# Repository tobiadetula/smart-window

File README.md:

# smart-window
detailing my final year project

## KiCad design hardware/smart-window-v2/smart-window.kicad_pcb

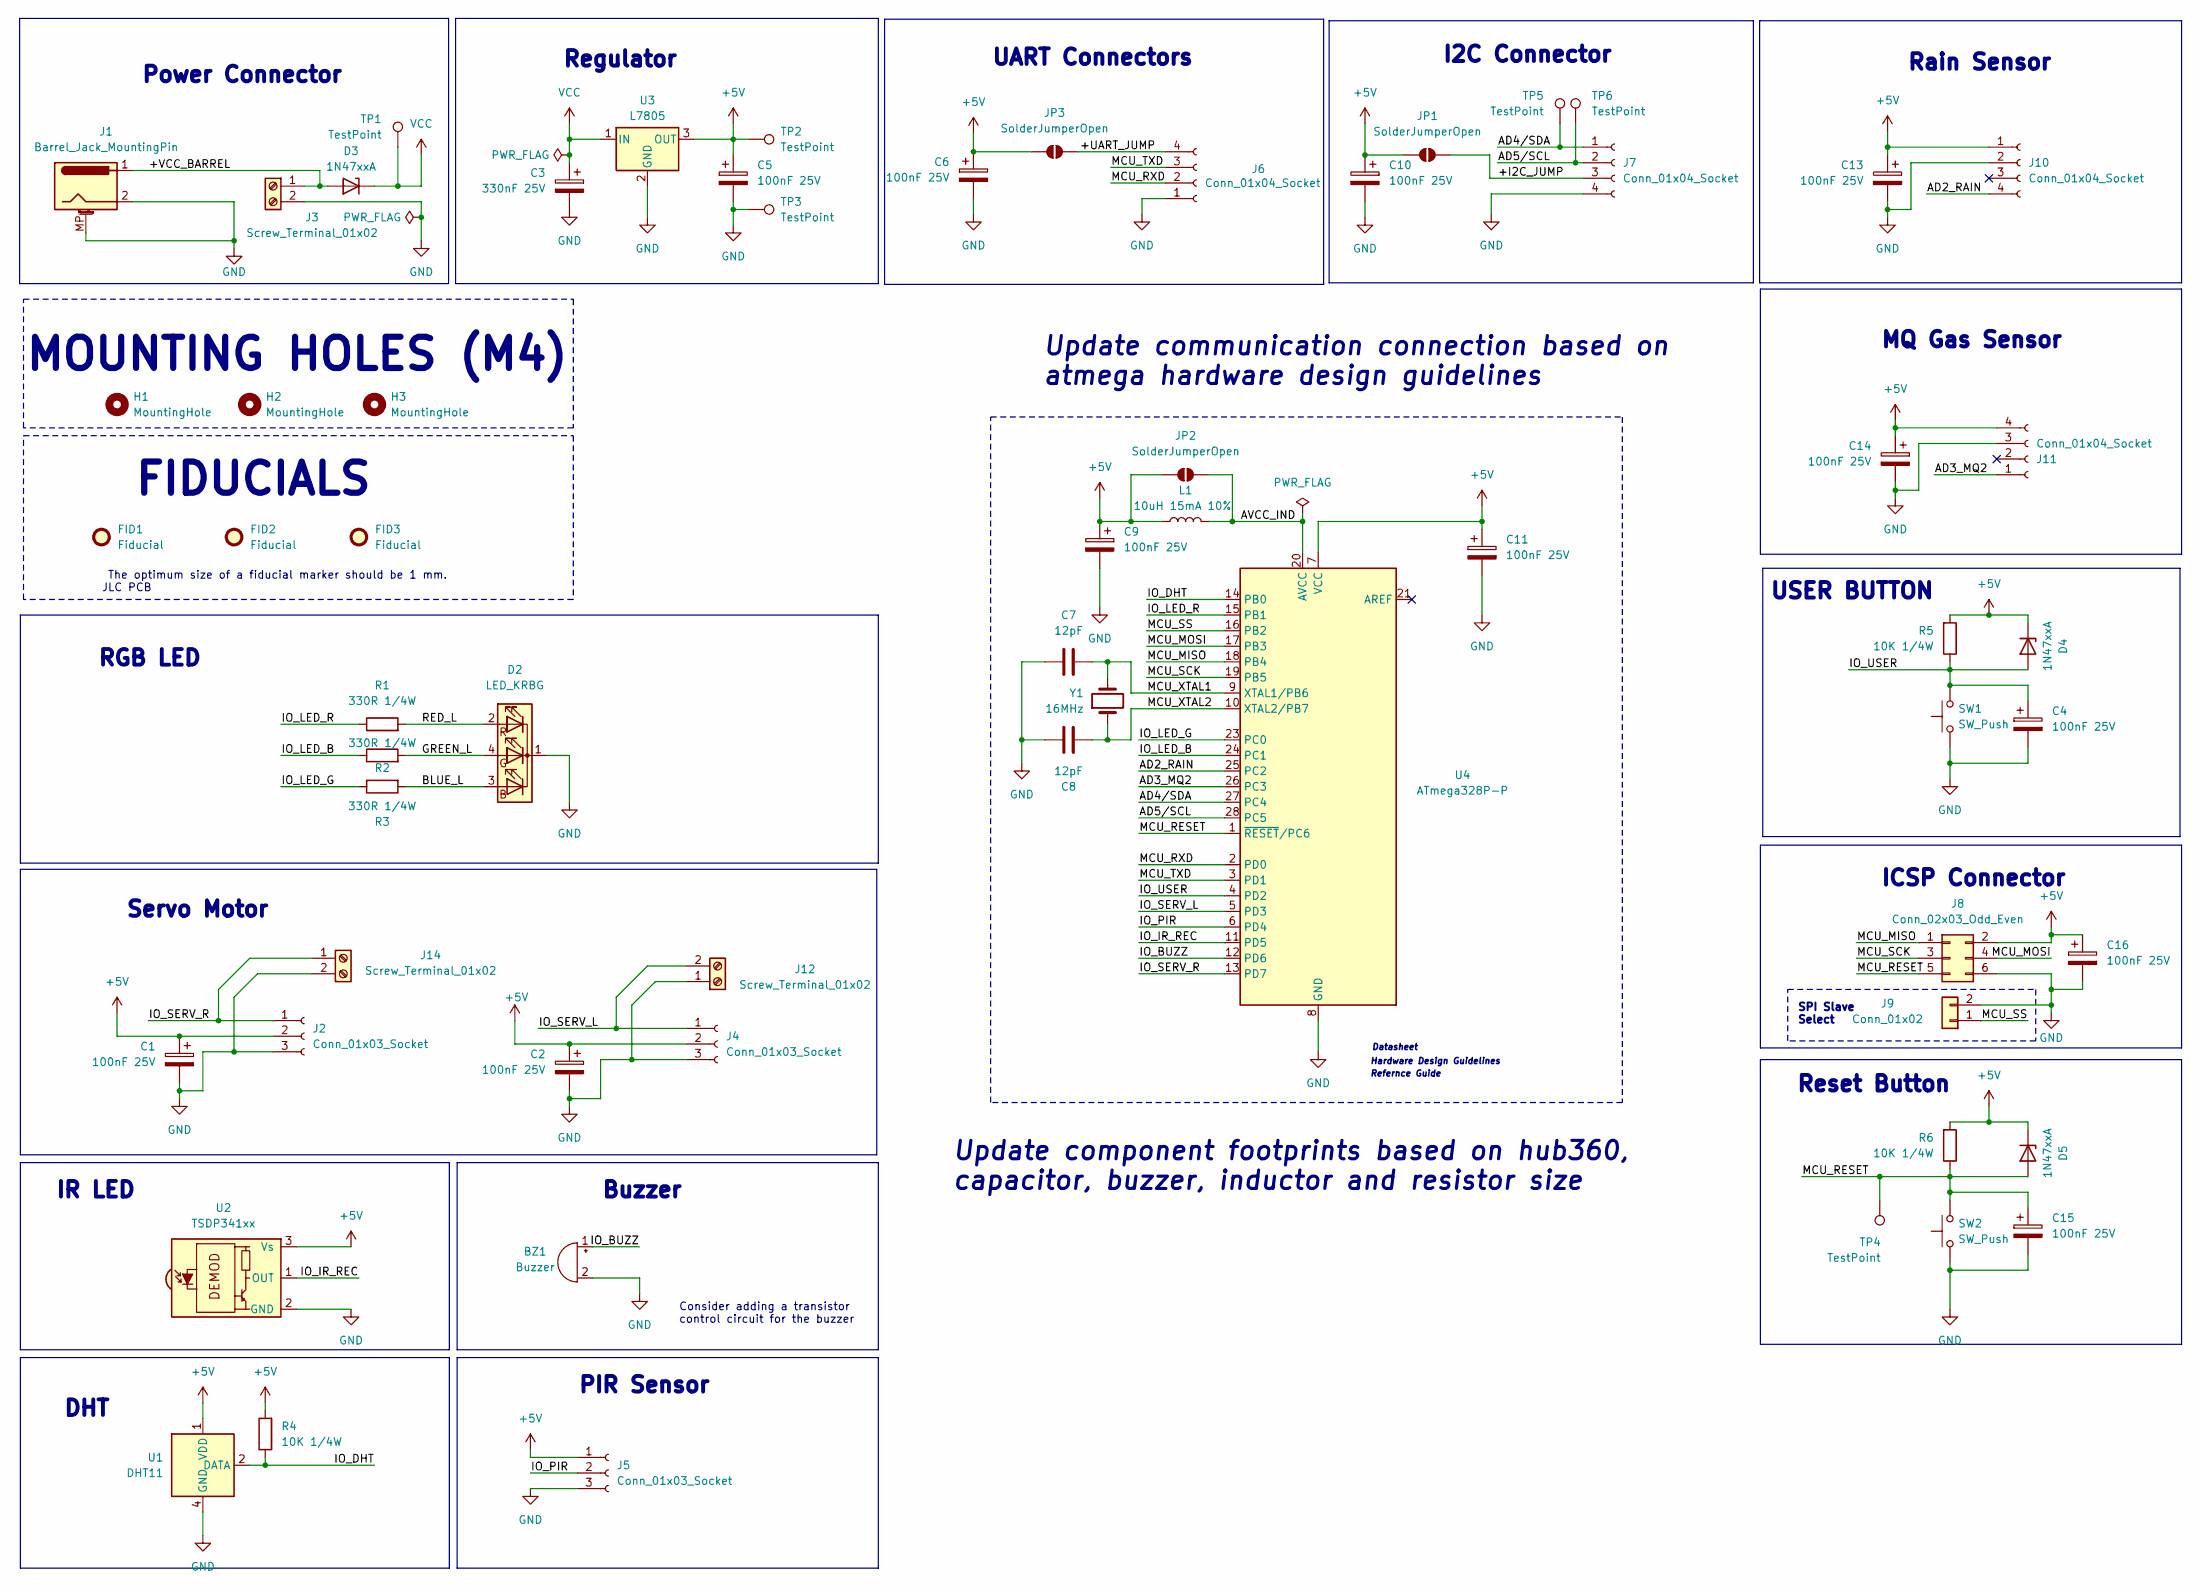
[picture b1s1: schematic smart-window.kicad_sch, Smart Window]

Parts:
BZ1: Buzzer; Buzzer_TDK_PS1240P02BT_D12.2mm_H6.5mm
C1, C2, C4, C5, C6, C9, C10, C11, C13, C14, C15, C16: 100nF 25V; CP_Radial_D4.0mm_P2.00mm
C3: 330nF 25V; CP_Radial_D4.0mm_P2.00mm
C7, C8: 12pF; C_Disc_D3.0mm_W2.0mm_P2.50mm
D2: LED_KRBG; LED_D5.0mm-4_RGB
D3, D4, D5: 1N47xxA; D_DO-41_SOD81_P10.16mm_Horizontal
FID1, FID2, FID3: Fiducial; Fiducial_1mm_Mask2mm
H1, H2, H3: MountingHole; MountingHole_4.3mm_M4
J1: Barrel_Jack_MountingPin; BarrelJack_Horizontal
J2, J4: Conn_01x03_Socket; Pins_1x03_2.54mm_TH
J3, J12, J14: Screw_Terminal_01x02; Altech_AK100_1x02_P5.00mm
J5: Conn_01x03_Socket; PinSocket_1x03_P2.54mm_Vertical
J6, J7, J10, J11: Conn_01x04_Socket; FanPinHeader_1x04_P2.54mm_Vertical
J8: Conn_02x03_Odd_Even; PinHeader_2x03_P2.54mm_Vertical
J9: Conn_01x02; PinSocket_1x02_P2.54mm_Vertical; Part Number 1-0201FBV0T
JP1, JP2, JP3: SolderJumperOpen; SolderJumper-2_P1.3mm_Open_TrianglePad1.0x1.5mm
L1: 10uH 15mA 10%; L_Axial_L5.3mm_D2.2mm_P10.16mm_Horizontal_Vishay_IM-1
R1, R2, R3: 330R 1/4W; R_Axial_DIN0207_L6.3mm_D2.5mm_P15.24mm_Horizontal
R4, R5, R6: 10K 1/4W; R_Axial_DIN0207_L6.3mm_D2.5mm_P15.24mm_Horizontal
SW1, SW2: SW_Push; SW_PUSH_6mm_H4.3mm
TP1, TP2, TP3, TP4, TP5, TP6: TestPoint; TestPoint_Pad_04
U1: DHT11; Aosong_DHT11_5.5x12.0_P2.54mm
U2: TSDP341xx; Vishay_MOLD-3Pin
U3: L7805; TO-220-3_Horizontal_TabDown
U4: ATmega328P-P; DIP-28_W7.62mm
Y1: 16MHz; Crystal_HC49-4H_Vertical

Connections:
+5V: C1.1, C2.1, C5.1, C6.1, C9.1, C10.1, C11.1, C13.1, C14.1, C16.1, D4.1 (K), D5.1 (K), J2.2, J4.2, J5.1, J8.2, J10.1, J11.4, JP1.1 (A), JP2.1 (A), JP3.1 (A), L1.1, R4.2, R5.2, R6.2, TP2.1, U1.1 (VDD), U2.3 (Vs), U3.3 (OUT), U4.7 (VCC)
/+I2C_JUMP: J7.3, JP1.2 (B)
/+UART_JUMP: J6.4, JP3.2 (B)
/+VCC_BARREL: D3.2 (A), J1.1, J3.1
/AD2_RAIN: J10.4, U4.25 (PC2)
/AD3_MQ2: J11.1, U4.26 (PC3)
/AD4/SDA: J7.1, TP5.1, U4.27 (PC4)
/AD5/SCL: J7.2, TP6.1, U4.28 (PC5)
/AVCC_IND: JP2.2 (B), L1.2, U4.20 (AVCC)
/BLUE_L: D2.3 (BA), R3.2
/GREEN_L: D2.4 (GA), R2.2
/IO_BUZZ: BZ1.1 (+), U4.12 (PD6)
/IO_DHT: R4.1, U1.2 (DATA), U4.14 (PB0)
/IO_IR_REC: U2.1 (OUT), U4.11 (PD5)
/IO_LED_B: R2.1, U4.24 (PC1)
/IO_LED_G: R3.1, U4.23 (PC0)
/IO_LED_R: R1.1, U4.15 (PB1)
/IO_PIR: J5.2, U4.6 (PD4)
/IO_SERV_L: J4.1, J12.2, U4.5 (PD3)
/IO_SERV_R: J2.1, J14.1, U4.13 (PD7)
/IO_USER: C4.1, D4.2 (A), R5.1, SW1.2, U4.4 (PD2)
/MCU_MISO: J8.1, U4.18 (PB4)
/MCU_MOSI: J8.4, U4.17 (PB3)
/MCU_RESET: C15.1, D5.2 (A), J8.5, R6.1, SW2.2, TP4.1, U4.1 (~RESET/PC6)
/MCU_RXD: J6.2, U4.2 (PD0)
/MCU_SCK: J8.3, U4.19 (PB5)
/MCU_SS: J9.1, U4.16 (PB2)
/MCU_TXD: J6.3, U4.3 (PD1)
/MCU_XTAL1: C7.2, U4.9 (XTAL1/PB6), Y1.2
/MCU_XTAL2: C8.2, U4.10 (XTAL2/PB7), Y1.1
/RED_L: D2.2 (RA), R1.2
GND: BZ1.2 (-), C1.2, C2.2, C3.2, C4.2, C5.2, C6.2, C7.1, C8.1, C9.2, C10.2, C11.2, C13.2, C14.2, C15.2, C16.2, D2.1 (K), J1.2, J1.MP (MountPin), J2.3, J3.2, J4.3, J5.3, J6.1, J7.4, J8.6, J9.2, J10.2, J11.3, J12.1, J14.2, SW1.1, SW2.1, TP3.1, U1.4 (GND), U2.2 (GND), U3.2 (GND), U4.8 (GND), U4.22 (GND)
VCC: C3.1, D3.1 (K), TP1.1, U3.1 (IN)

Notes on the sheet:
RGB LED
Hardware Design Guidelines
Consider adding a transistor control circuit for the buzzer
IR LED
I2C Connector
Refernce Guide
MOUNTING HOLES (M4)
Update component footprints based on hub360, capacitor, buzzer, inductor and resistor size
Rain Sensor
USER BUTTON
The optimum size of a fiducial marker should be 1 mm. JLC PCB
MQ Gas Sensor
UART Connectors
ICSP Connector
Reset Button
Regulator
PIR Sensor
Update communication connection based on atmega hardware design guidelines
FIDUCIALS
Datasheet
Servo Motor
DHT
Buzzer
SPI Slave Select
Power Connector

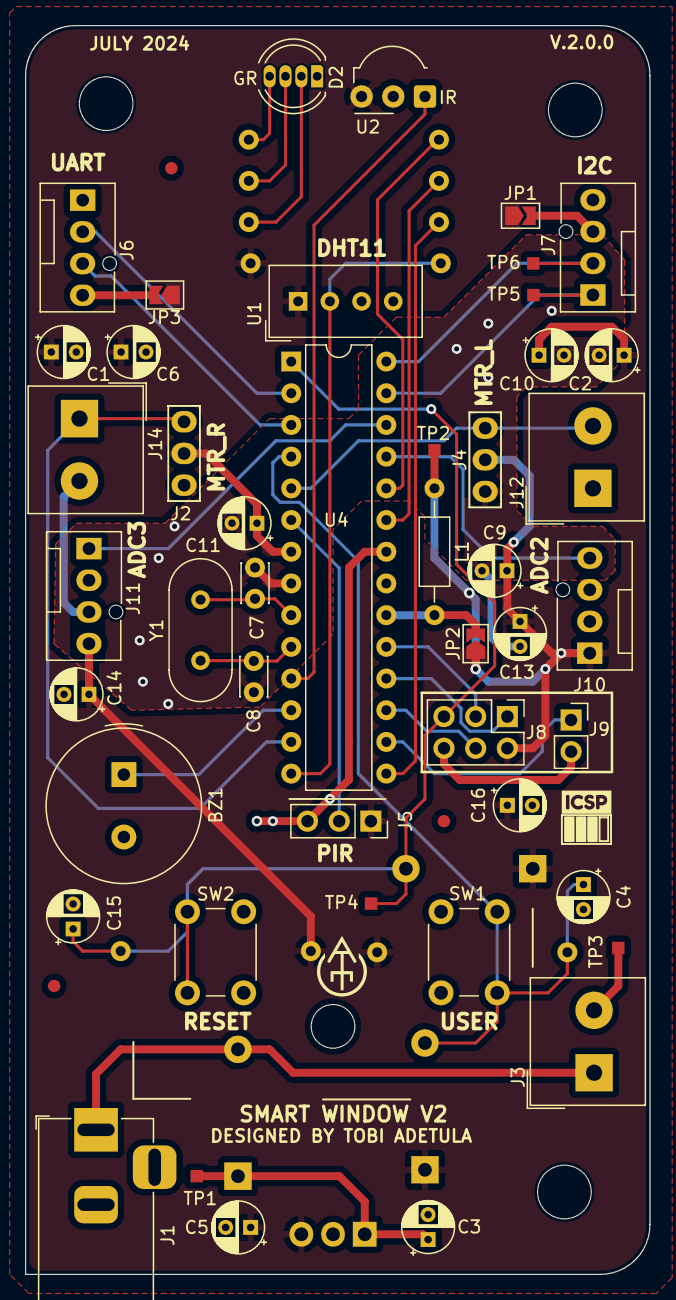
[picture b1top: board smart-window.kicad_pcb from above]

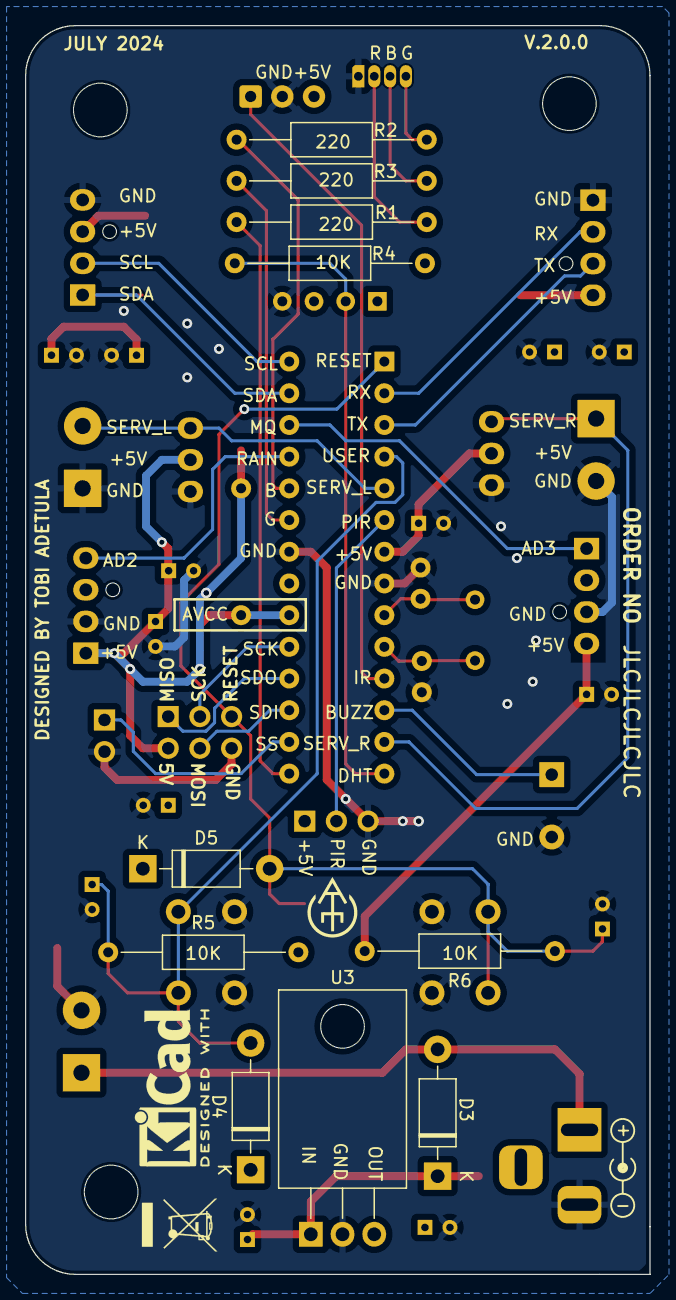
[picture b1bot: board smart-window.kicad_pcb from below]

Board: 2 copper layers, 50.0 x 100.1 mm, 65 parts (11 on the bottom side), 33 nets.

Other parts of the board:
G1, G1#2: LOGO; Insignia_mini
kibuzzard-64D226C5: G***; kibuzzard-64D226C5

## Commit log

2024-02-25 Initial Commit:
2024-03-22 Project Structure Reorganization
2024-03-22 Schematic File for Smart Window V2 Completed
2024-04-15 Schematic Completed
2024-04-22 Draft of PCB Arragement Complete
2024-05-12 chore(git): organise gitignore and tracking structure
2024-07-03 pcb design silkscreen in progress
2024-07-11 submitted files to jlc for manufacturing
2024-07-11 Updated submodule to the latest commit
